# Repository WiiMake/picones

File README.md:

# PicoNES Cartridge

In the last 40 years, technology has advanced to the point were what used to be
done in hardware can now be done in software. This project uses an rp2350 to
emulate a ROM chip on an NES Cartridge.

Documentation Unfinished

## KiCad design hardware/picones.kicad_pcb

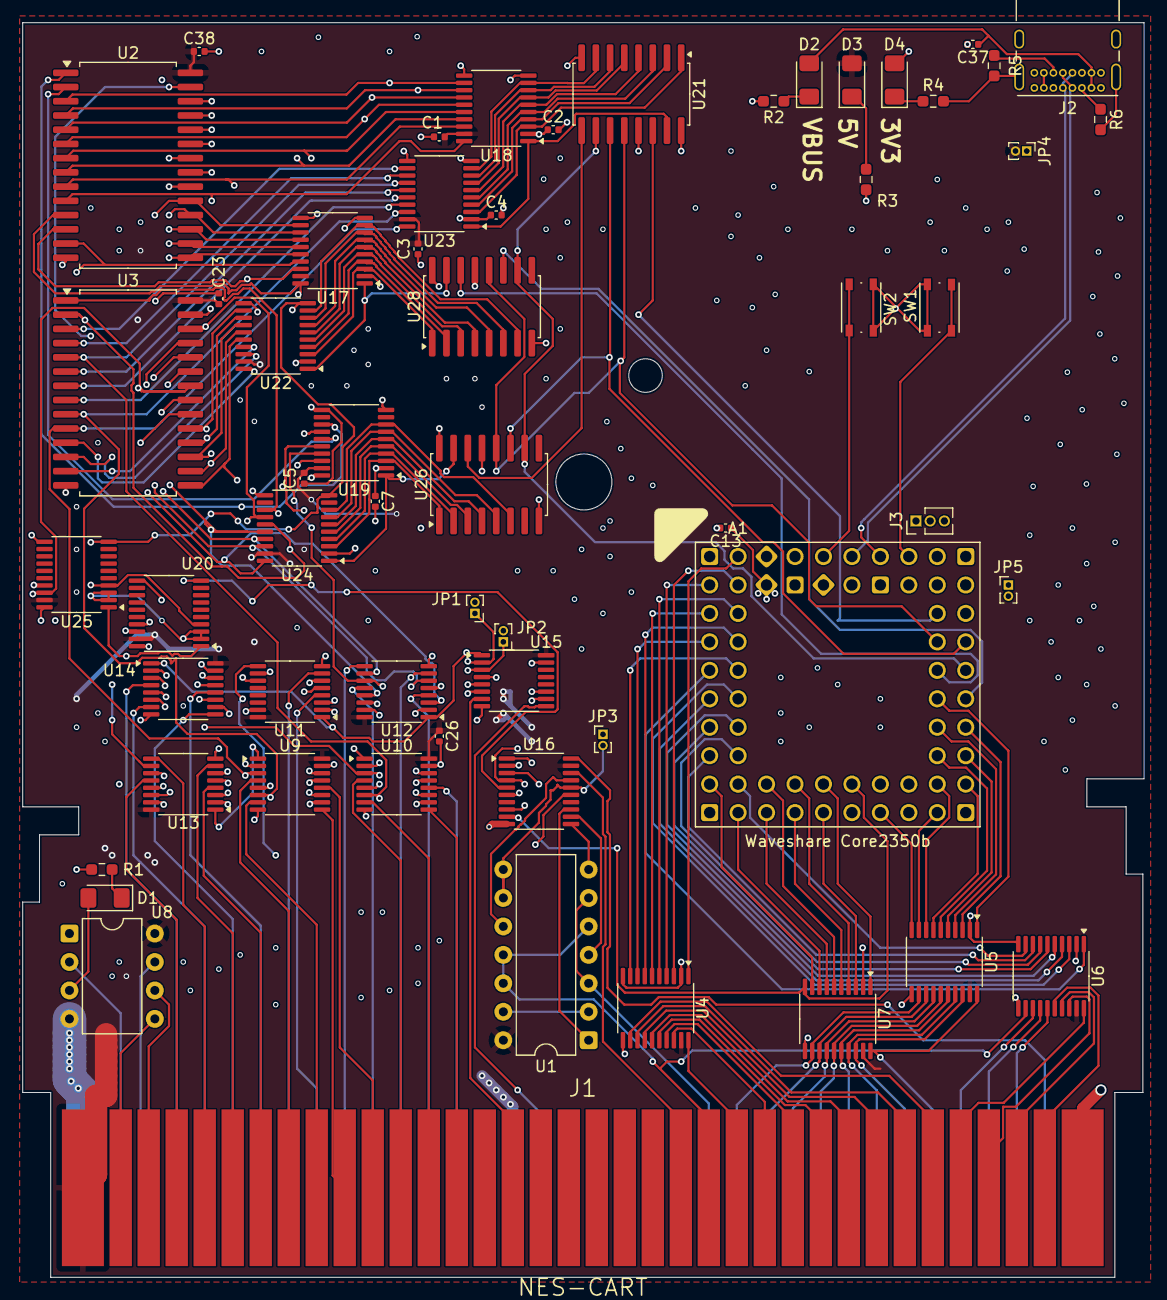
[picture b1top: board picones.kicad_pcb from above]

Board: 6 copper layers, 100.1 x 112.0 mm, 59 parts (0 on the bottom side), 201 nets.

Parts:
A1: Waveshare Core2350b; waveshare_core2350b
C1, C2, C3, C4, C5, C7, C13, C23, C26: .1u; C_0402_1005Metric
C37, C38: 10u; C_0402_1005Metric
D1, D2, D3, D4: LED; LED_1206_3216Metric_Pad1.42x1.75mm_HandSolder
J1: NES-CART; NES_CART_FINGERS
J2: USB_C_Receptacle_USB2.0_14P; USB_C_Receptacle_GCT_USB4085
J3: Conn_01x03; PinHeader_1x03_P1.27mm_Vertical
JP1: Mem 1 CE to GND; PinHeader_1x02_P1.00mm_Vertical
JP2: Mem 2 CE to GND; PinHeader_1x02_P1.00mm_Vertical
JP3: Disable Mem Swapping; PinHeader_1x02_P1.00mm_Vertical
JP4: VBUS to 5v; PinHeader_1x02_P1.00mm_Vertical
JP5: Connect Pico Mem CE and WE; PinHeader_1x02_P1.00mm_Vertical
R1, R2, R3, R4, R5, R6: 5.1k; R_0603_1608Metric_Pad0.98x0.95mm_HandSolder
SW1: Bootsel; SW_Push_1P1T_NO_Vertical_Wuerth_434133025816
SW2: Reset; SW_Push_1P1T_NO_Vertical_Wuerth_434133025816
U1: 74HC02; DIP-14_W7.62mm
U2, U3: IS62C256AL; SOP-28_8.4x18.16mm_P1.27mm
U4, U5, U6, U7, U16, U17, U18, U19, U20, U22, U23, U24, U25: TXS0108EPW; TSSOP-20_4.4x6.5mm_P0.65mm
U8: ATtiny13A-P; DIP-8_W7.62mm
U9, U10, U11, U12, U13, U14, U15: TMUX1574PW; TSSOP-16_4.4x5mm_P0.65mm
U21, U26, U28: 74HC595; SOIC-16W_5.3x10.2mm_P1.27mm

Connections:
+3.3V: A1.55 (3V3), C2.1, C4.1, C7.1, C13.1, D4.2 (A), U4.2 (VCCA), U4.10 (OE), U5.2 (VCCA), U6.2 (VCCA), U6.10 (OE), U7.2 (VCCA), U16.2 (VCCA), U16.10 (OE), U17.2 (VCCA), U18.2 (VCCA), U19.2 (VCCA), U20.2 (VCCA), U20.3 (A2), U21.16 (VCC), U22.2 (VCCA), U23.2 (VCCA), U24.2 (VCCA), U25.2 (VCCA), U25.3 (A2), U26.16 (VCC), U28.16 (VCC)
+5V: C1.1, C3.1, C5.1, C23.1, C26.1, C38.1, D3.2 (A), J1.36 (VCC), J1.57 (~VCS), JP4.2 (B), U1.14 (VCC), U2.28 (VDD), U3.28 (VDD), U4.19 (VCCB), U5.19 (VCCB), U6.19 (VCCB), U7.19 (VCCB), U8.8 (VCC), U9.16 (VDD), U10.16 (VDD), U11.16 (VDD), U12.16 (VDD), U13.16 (VDD), U14.16 (VDD), U15.16 (VDD), U16.19 (VCCB), U17.19 (VCCB), U18.19 (VCCB), U19.19 (VCCB), U20.19 (VCCB), U22.19 (VCCB), U23.19 (VCCB), U24.19 (VCCB), U25.19 (VCCB)
/CIC_CLK: J1.71 (4MHz), U8.2 (PB3)
/CIC_DIN: J1.34 (S0), U8.6 (PB1)
/CIC_DOUT: J1.35 (S1), U8.5 (PB0)
/CIC_RST: J1.70 (S2), U8.7 (PB2)
/CPU_A0: J1.13 (A0), U4.20 (B1)
/CPU_A1: J1.12 (A1), U4.18 (B2)
/CPU_A2: J1.11 (A2), U4.17 (B3)
/CPU_A3: J1.10 (A3), U4.16 (B4)
/CPU_A4: J1.9 (A4), U4.15 (B5)
/CPU_A5: J1.8 (A5), U4.14 (B6)
/CPU_A6: J1.7 (A6), U4.13 (B7)
/CPU_A7: J1.6 (A7), U4.12 (B8)
/CPU_A8: J1.5 (A8), U6.20 (B1)
/CPU_A9: J1.4 (A9), U6.18 (B2)
/CPU_A10: J1.3 (A10), U6.17 (B3)
/CPU_A11: J1.2 (A11), U6.16 (B4)
/CPU_A12: J1.39 (A12), U6.15 (B5)
/CPU_A13: J1.40 (A13), U6.14 (B6)
/CPU_A14: J1.41 (A14), U6.13 (B7)
/CPU_CLK: J1.38 (PHI2), U16.20 (B1)
/CPU_D0: J1.49 (D0), U5.12 (B8), U7.12 (B8)
/CPU_D1: J1.48 (D1), U5.13 (B7), U7.13 (B7)
/CPU_D2: J1.47 (D2), U5.14 (B6), U7.14 (B6)
/CPU_D3: J1.46 (D3), U5.15 (B5), U7.15 (B5)
/CPU_D4: J1.45 (D4), U5.16 (B4), U7.16 (B4)
/CPU_D5: J1.44 (D5), U5.17 (B3), U7.17 (B3)
/CPU_D6: J1.43 (D6), U5.18 (B2), U7.18 (B2)
/CPU_D7: J1.42 (D7), U5.20 (B1), U7.20 (B1)
/CPU_IRQ: J1.15 (~IRQ), U16.18 (B2)
/CPU_ROMSEL: J1.50 (~PRG), U1.3, U1.6
/CPU_R/!W: J1.14 (R/~W), U1.5, U1.11, U1.12, U6.12 (B8)
/MEM_1_!CE: JP1.1 (A), U2.20 (~CE), U15.2 (S1A), U20.20 (B1)
/MEM_1_!OE: U2.22 (~OE), U15.5 (S2A), U20.18 (B2)
/MEM_1_!WE: U2.27 (~WE), U15.11 (S3A), U20.17 (B3)
/MEM_1_A0: U2.10 (A0), U9.2 (S1A), U18.20 (B1)
/MEM_1_A1: U2.9 (A1), U9.5 (S2A), U18.18 (B2)
/MEM_1_A2: U2.8 (A2), U9.11 (S3A), U18.17 (B3)
/MEM_1_A3: U2.7 (A3), U9.14 (S4A), U18.16 (B4)
/MEM_1_A4: U2.6 (A4), U10.2 (S1A), U18.15 (B5)
/MEM_1_A5: U2.5 (A5), U10.5 (S2A), U18.14 (B6)
/MEM_1_A6: U2.4 (A6), U10.11 (S3A), U18.13 (B7)
/MEM_1_A7: U2.3 (A7), U10.14 (S4A), U18.12 (B8)
/MEM_1_A8: U2.25 (A8), U12.2 (S1A), U19.20 (B1)
/MEM_1_A9: U2.24 (A9), U12.5 (S2A), U19.18 (B2)
/MEM_1_A10: U2.21 (A10), U12.11 (S3A), U19.17 (B3)
/MEM_1_A11: U2.23 (A11), U12.14 (S4A), U19.16 (B4)
/MEM_1_A12: U2.2 (A12), U11.2 (S1A), U19.15 (B5)
/MEM_1_A13: U2.26 (A13), U11.5 (S2A), U19.14 (B6)
/MEM_1_A14: U2.1 (A14), U11.11 (S3A), U19.13 (B7)
/MEM_1_D0: U2.11 (I/O0), U13.2 (S1A), U17.20 (B1)
/MEM_1_D1: U2.12 (I/O1), U13.5 (S2A), U17.18 (B2)
/MEM_1_D2: U2.13 (I/O2), U13.11 (S3A), U17.17 (B3)
/MEM_1_D3: U2.15 (I/O3), U13.14 (S4A), U17.16 (B4)
/MEM_1_D4: U2.16 (I/O4), U14.2 (S1A), U17.15 (B5)
/MEM_1_D5: U2.17 (I/O5), U14.5 (S2A), U17.14 (B6)
/MEM_1_D6: U2.18 (I/O6), U14.11 (S3A), U17.13 (B7)
/MEM_1_D7: U2.19 (I/O7), U14.14 (S4A), U17.12 (B8)
/MEM_2_!CE: JP2.1 (A), U3.20 (~CE), U15.3 (S1B), U25.20 (B1)
/MEM_2_!OE: U3.22 (~OE), U15.6 (S2B), U25.18 (B2)
/MEM_2_!WE: U3.27 (~WE), U15.10 (S3B), U25.17 (B3)
/MEM_2_A0: U3.10 (A0), U9.3 (S1B), U23.20 (B1)
/MEM_2_A1: U3.9 (A1), U9.6 (S2B), U23.18 (B2)
/MEM_2_A2: U3.8 (A2), U9.10 (S3B), U23.17 (B3)
/MEM_2_A3: U3.7 (A3), U9.13 (S4B), U23.16 (B4)
/MEM_2_A4: U3.6 (A4), U10.3 (S1B), U23.15 (B5)
/MEM_2_A5: U3.5 (A5), U10.6 (S2B), U23.14 (B6)
/MEM_2_A6: U3.4 (A6), U10.10 (S3B), U23.13 (B7)
/MEM_2_A7: U3.3 (A7), U10.13 (S4B), U23.12 (B8)
/MEM_2_A8: U3.25 (A8), U12.3 (S1B), U24.20 (B1)
/MEM_2_A9: U3.24 (A9), U12.6 (S2B), U24.18 (B2)
/MEM_2_A10: U3.21 (A10), U12.10 (S3B), U24.17 (B3)
/MEM_2_A11: U3.23 (A11), U12.13 (S4B), U24.16 (B4)
/MEM_2_A12: U3.2 (A12), U11.3 (S1B), U24.15 (B5)
/MEM_2_A13: U3.26 (A13), U11.6 (S2B), U24.14 (B6)
/MEM_2_A14: U3.1 (A14), U11.10 (S3B), U24.13 (B7)
/MEM_2_D0: U3.11 (I/O0), U13.3 (S1B), U22.20 (B1)
/MEM_2_D1: U3.12 (I/O1), U13.6 (S2B), U22.18 (B2)
/MEM_2_D2: U3.13 (I/O2), U13.10 (S3B), U22.17 (B3)
/MEM_2_D3: U3.15 (I/O3), U13.13 (S4B), U22.16 (B4)
/MEM_2_D4: U3.16 (I/O4), U14.3 (S1B), U22.15 (B5)
/MEM_2_D5: U3.17 (I/O5), U14.6 (S2B), U22.14 (B6)
/MEM_2_D6: U3.18 (I/O6), U14.10 (S3B), U22.13 (B7)
/MEM_2_D7: U3.19 (I/O7), U14.13 (S4B), U22.12 (B8)
/MEM_SEL_1/!2: U1.10, U16.17 (B3)
/MEM_SEL_1/!2_3V3: A1.24 (GPIO24), U16.4 (A3), U22.10 (OE), U23.10 (OE), U24.10 (OE), U25.10 (OE)
/MEM_SEL_!1/2: JP3.2 (B), U1.8, U1.9, U9.1 (SEL), U10.1 (SEL), U11.1 (SEL), U12.1 (SEL), U13.1 (SEL), U14.1 (SEL), U15.1 (SEL), U16.16 (B4)
/MEM_SEL_!1/2_3V3: U16.5 (A4), U17.10 (OE), U18.10 (OE), U19.10 (OE), U20.10 (OE)
/MEM_SEL_PPU_BANK: U11.9 (D3), U16.15 (B5)
/PICO_CPU_A0: A1.0 (GPIO0), U4.1 (A1)
/PICO_CPU_A1: A1.1 (GPIO1), U4.3 (A2)
/PICO_CPU_A2: A1.2 (GPIO2), U4.4 (A3)
/PICO_CPU_A3: A1.3 (GPIO3), U4.5 (A4)
/PICO_CPU_A4: A1.4 (GPIO4), U4.6 (A5)
/PICO_CPU_A5: A1.5 (GPIO5), U4.7 (A6)
/PICO_CPU_A6: A1.6 (GPIO6), U4.8 (A7)
/PICO_CPU_A7: A1.7 (GPIO7), U4.9 (A8)
/PICO_CPU_A8: A1.8 (GPIO8), U6.1 (A1)
/PICO_CPU_A9: A1.9 (GPIO9), U6.3 (A2)
/PICO_CPU_A10: A1.10 (GPIO10), U6.4 (A3)
/PICO_CPU_A11: A1.11 (GPIO11), U6.5 (A4)
/PICO_CPU_A12: A1.12 (GPIO12), U6.6 (A5)
/PICO_CPU_A13: A1.13 (GPIO13), U6.7 (A6)
/PICO_CPU_A14: A1.14 (GPIO14), U6.8 (A7)
/PICO_CPU_CLK: A1.27 (GPIO27), U16.1 (A1)
/PICO_CPU_D0_R: A1.30 (GPIO30), U5.9 (A8)
/PICO_CPU_D0_W: A1.16 (GPIO16), U7.9 (A8)
/PICO_CPU_D1_R: A1.31 (GPIO31), U5.8 (A7)
/PICO_CPU_D1_W: A1.17 (GPIO17), U7.8 (A7)
/PICO_CPU_D2_R: A1.32 (GPIO32), U5.7 (A6)
/PICO_CPU_D2_W: A1.18 (GPIO18), U7.7 (A6)
/PICO_CPU_D3_R: A1.33 (GPIO33), U5.6 (A5)
/PICO_CPU_D3_W: A1.19 (GPIO19), U7.6 (A5)
/PICO_CPU_D4_R: A1.34 (GPIO34), U5.5 (A4)
/PICO_CPU_D4_W: A1.20 (GPIO20), U7.5 (A4)
/PICO_CPU_D5_R: A1.35 (GPIO35), U5.4 (A3)
/PICO_CPU_D5_W: A1.21 (GPIO21), U7.4 (A3)
/PICO_CPU_D6_R: A1.36 (GPIO36), U5.3 (A2)
/PICO_CPU_D6_W: A1.22 (GPIO22), U7.3 (A2)
/PICO_CPU_D7_R: A1.37 (GPIO37), U5.1 (A1)
/PICO_CPU_D7_W: A1.23 (GPIO23), U7.1 (A1)
/PICO_CPU_IRQ: A1.28 (GPIO28), U16.3 (A2)
/PICO_CPU_R/!W: A1.15 (GPIO15), U6.9 (A8)
/PICO_MEM_!CE: A1.46 (GPIO46_ADC6), JP5.1 (A), U20.1 (A1), U25.1 (A1)
/PICO_MEM_!WE: A1.45 (GPIO45_ADC5), JP5.2 (B), U20.4 (A3), U25.4 (A3)
/PICO_MEM_A0: U18.1 (A1), U21.15 (QA), U23.1 (A1)
/PICO_MEM_A1: U18.3 (A2), U21.1 (QB), U23.3 (A2)
/PICO_MEM_A2: U18.4 (A3), U21.2 (QC), U23.4 (A3)
/PICO_MEM_A3: U18.5 (A4), U21.3 (QD), U23.5 (A4)
/PICO_MEM_A4: U18.6 (A5), U21.4 (QE), U23.6 (A5)
/PICO_MEM_A5: U18.7 (A6), U21.5 (QF), U23.7 (A6)
/PICO_MEM_A6: U18.8 (A7), U21.6 (QG), U23.8 (A7)
/PICO_MEM_A7: U18.9 (A8), U21.7 (QH), U23.9 (A8)
/PICO_MEM_A8: U19.1 (A1), U24.1 (A1), U26.15 (QA)
/PICO_MEM_A9: U19.3 (A2), U24.3 (A2), U26.1 (QB)
/PICO_MEM_A10: U19.4 (A3), U24.4 (A3), U26.2 (QC)
/PICO_MEM_A11: U19.5 (A4), U24.5 (A4), U26.3 (QD)
/PICO_MEM_A12: U19.6 (A5), U24.6 (A5), U26.4 (QE)
/PICO_MEM_A13: U19.7 (A6), U24.7 (A6), U26.5 (QF)
/PICO_MEM_A14: U19.8 (A7), U24.8 (A7), U26.6 (QG)
/PICO_MEM_D0: U17.1 (A1), U22.1 (A1), U28.15 (QA)
/PICO_MEM_D1: U17.3 (A2), U22.3 (A2), U28.1 (QB)
/PICO_MEM_D2: U17.4 (A3), U22.4 (A3), U28.2 (QC)
/PICO_MEM_D3: U17.5 (A4), U22.5 (A4), U28.3 (QD)
/PICO_MEM_D4: U17.6 (A5), U22.6 (A5), U28.4 (QE)
/PICO_MEM_D5: U17.7 (A6), U22.7 (A6), U28.5 (QF)
/PICO_MEM_D6: U17.8 (A7), U22.8 (A7), U28.6 (QG)
/PICO_MEM_D7: U17.9 (A8), U22.9 (A8), U28.7 (QH)
/PICO_MEM_SEL_PPU_BANK: A1.29 (GPIO29), U16.6 (A5)
/PICO_PPU_!CLR: A1.40 (GPIO40_ADC0), U21.10 (~SRCLR), U26.10 (~SRCLR), U28.10 (~SRCLR)
/PICO_PPU_ADDR_CLK: A1.42 (GPIO42_ADC2), U21.11 (SRCLK), U26.11 (SRCLK)
/PICO_PPU_ADDR_SIN: A1.43 (GPIO43_ADC3), U21.14 (SER)
/PICO_PPU_DATA_CLK: A1.38 (GPIO38), U28.11 (SRCLK)
/PICO_PPU_DATA_SIN: A1.39 (GPIO39), U28.14 (SER)
/PICO_PPU_LATCH: A1.41 (GPIO41_ADC1), U21.12 (RCLK), U26.12 (RCLK), U28.12 (RCLK)
/PPU_!R: J1.21 (~R), U15.7 (D2)
/PPU_!W: J1.56 (~W), U15.9 (D3)
/PPU_A0: J1.29 (A0), U9.4 (D1)
/PPU_A1: J1.28 (A1), U9.7 (D2)
/PPU_A2: J1.27 (A2), U9.9 (D3)
/PPU_A3: J1.26 (A3), U9.12 (D4)
/PPU_A4: J1.25 (A4), U10.4 (D1)
/PPU_A5: J1.24 (A5), U10.7 (D2)
/PPU_A6: J1.23 (A6), U10.9 (D3)
/PPU_A7: J1.59 (A7), U10.12 (D4)
/PPU_A8: J1.60 (A8), U12.4 (D1)
/PPU_A9: J1.61 (A9), U12.7 (D2)
/PPU_A10: J1.63 (A10), U12.9 (D3)
/PPU_A11: J1.62 (A11), U12.12 (D4)
/PPU_A12: J1.64 (A12), U11.4 (D1)
/PPU_A13: J1.65 (A13), U11.7 (D2)
/PPU_D0: J1.30 (D0), U13.4 (D1)
/PPU_D1: J1.31 (D1), U13.7 (D2)
/PPU_D2: J1.32 (D2), U13.9 (D3)
/PPU_D3: J1.33 (D3), U13.12 (D4)
/PPU_D4: J1.69 (D4), U14.4 (D1)
/PPU_D5: J1.68 (D5), U14.7 (D2)
/PPU_D6: J1.67 (D6), U14.9 (D3)
/PPU_D7: J1.66 (D7), U14.12 (D4)
/ROE: U1.1, U16.13 (B7)
/ROE_3V3: A1.26 (GPIO26), U5.10 (OE), U16.8 (A7)
/USB_D+: A1.52 (USB_DP), J2.A6 (D+), J2.B6 (D+)
/USB_D-: A1.50 (USB_DM), J2.A7 (D-), J2.B7 (D-)
/WIT: U1.4, U16.12 (B8)
/WIT_3V3: A1.25 (GPIO25), U7.10 (OE), U16.9 (A8)
GND: A1.58 (GND), A1.59 (GND), A1.60 (GND), A1.61 (GND), A1.62 (GND), A1.63 (GND), C1.2, C2.2, C3.2, C4.2, C5.2, C7.2, C13.2, C23.2, C26.2, C37.2, C38.2, J1.1 (GND), J1.72 (GND), J2.A1 (GND), J2.A12 (GND), J2.B1 (GND), J2.B12 (GND), J2.S1 (SHIELD), J3.1, JP1.2 (B), JP2.2 (B), JP3.1 (A), R1.2, R2.2, R3.2, R4.2, R5.2, R6.2, SW1.1, SW2.1, U1.7 (GND), U2.14 (GND), U3.14 (GND), U4.11 (GND), U5.11 (GND), U6.11 (GND), U7.11 (GND), U8.4 (GND), U9.8 (GND), U9.15 (~EN), U10.8 (GND), U10.15 (~EN), U11.8 (GND), U11.15 (~EN), U12.8 (GND), U12.15 (~EN), U13.8 (GND), U13.15 (~EN), U14.8 (GND), U14.15 (~EN), U15.4 (D1), U15.8 (GND), U15.15 (~EN), U16.11 (GND), U17.11 (GND), U18.11 (GND), U19.11 (GND), U20.11 (GND), U21.8 (GND), U21.13 (~OE), U22.11 (GND), U23.11 (GND), U24.11 (GND), U25.11 (GND), U26.8 (GND), U26.13 (~OE), U28.8 (GND), U28.13 (~OE)
unnamed: A1.48 (BOOTSEL), SW1.2
unnamed: A1.54 (RUN), SW2.2
unnamed: A1.51 (SWCLK), J3.2
unnamed: A1.49 (SWDIO), J3.3
unnamed: D1.2 (A), U8.3 (PB4)
unnamed: D1.1 (K), R1.1
unnamed: D2.1 (K), R2.1
unnamed: D3.1 (K), R3.1
unnamed: D4.1 (K), R4.1
unnamed: J2.A5 (CC1), R6.1
unnamed: J2.B5 (CC2), R5.1
unnamed: U1.2, U1.13
unnamed: U21.9 (QH'), U26.14 (SER)
VBUS: A1.57 (VBUS), C37.1, D2.2 (A), J2.A4 (VBUS), J2.A9 (VBUS), J2.B4 (VBUS), J2.B9 (VBUS), JP4.1 (A)

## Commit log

2025-10-18 current working code
2025-10-18 initial audio commit; config still not working with mmc1 mapper
2025-10-18 updated cmake file, built project
2025-10-19 4 channels work; DPCM does not and is currently reading from (which is the code), creating random noises
2025-10-19 updated to mmc3; dpcm sample playback still not working
2025-10-25 initial schematics
2025-11-05 route attempt 1
2025-11-17 v1 pcb
2025-12-05 small changes
